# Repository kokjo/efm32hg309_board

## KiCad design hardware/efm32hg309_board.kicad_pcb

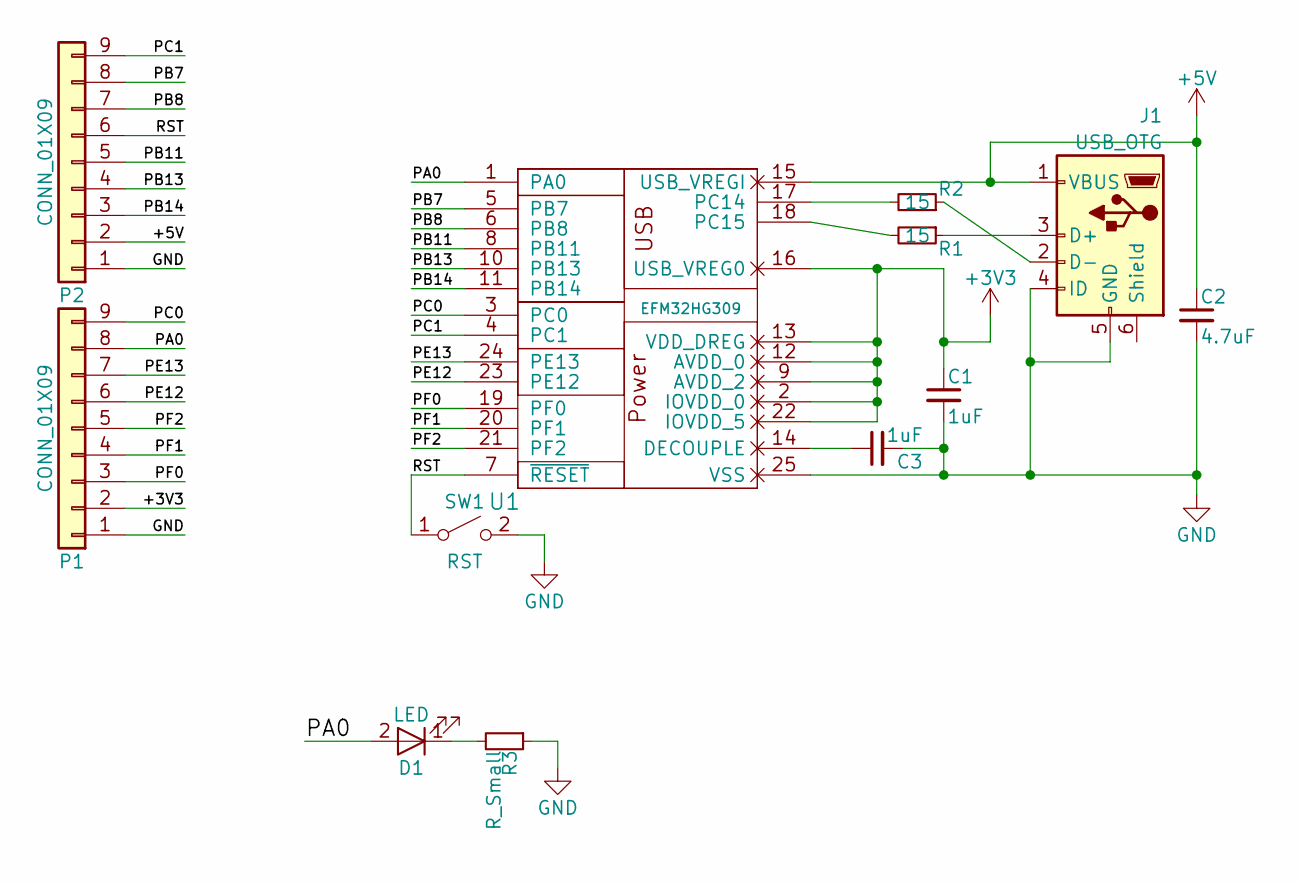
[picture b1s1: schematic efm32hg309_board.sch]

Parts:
C1, C3: 1uF; C_0805
C2: 4.7uF; C_0805
D1: LED; LED_0805
J1: USB_OTG; USB_Micro-B_Molex_47346-0001
P1, P2: CONN_01X09; Pin_Header_Straight_1x09
R1, R2: 15; R_0805
R3: R_Small; R_0805
SW1: RST; SW_SPST_B3U-1000P
U1: EFM32HG309; QFN-24-1EP_5x5mm_Pitch0.65mm

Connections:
+3V3: C1.1, P1.2, U1.2 (IOVDD_0), U1.9 (AVDD_2), U1.12 (AVDD_0), U1.13 (VDD_DREG), U1.16 (USB_VREG0), U1.22 (IOVDD_5)
+5V: C2.1, J1.1 (VBUS), P2.2, U1.15 (USB_VREGI)
/PA0: D1.2 (A), P1.8, U1.1 (PA0)
/PB7: P2.8, U1.5 (PB7)
/PB8: P2.7, U1.6 (PB8)
/PB11: P2.5, U1.8 (PB11)
/PB13: P2.4, U1.10 (PB13)
/PB14: P2.3, U1.11 (PB14)
/PC0: P1.9, U1.3 (PC0)
/PC1: P2.9, U1.4 (PC1)
/PE12: P1.6, U1.23 (PE12)
/PE13: P1.7, U1.24 (PE13)
/PF0: P1.3, U1.19 (PF0)
/PF1: P1.4, U1.20 (PF1)
/PF2: P1.5, U1.21 (PF2)
/RST: P2.6, SW1.1 (A), U1.7 (~RESET)
GND: C1.2, C2.2, C3.2, J1.4 (ID), J1.5 (GND), P1.1, P2.1, R3.1, SW1.2 (B), U1.25 (VSS)
unnamed: C3.1, U1.14 (DECOUPLE)
unnamed: D1.1 (K), R3.2
unnamed: J1.2 (D-), R2.1
unnamed: J1.3 (D+), R1.1
unnamed: R1.2, U1.18 (PC15)
unnamed: R2.2, U1.17 (PC14)

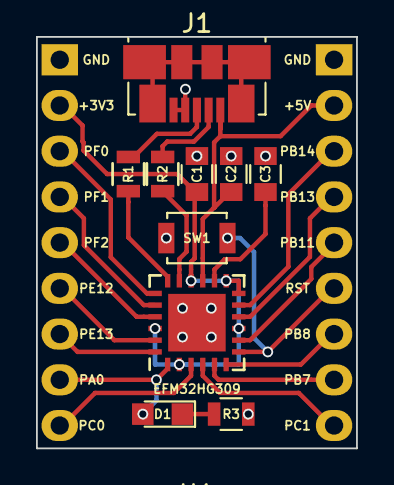
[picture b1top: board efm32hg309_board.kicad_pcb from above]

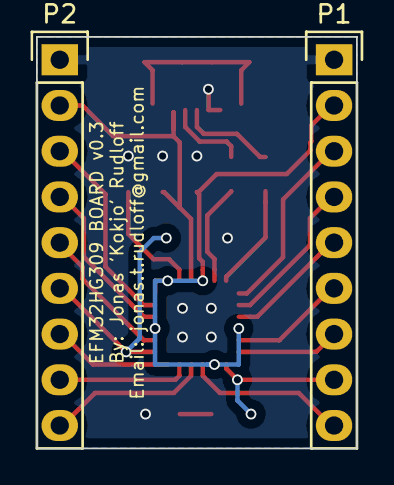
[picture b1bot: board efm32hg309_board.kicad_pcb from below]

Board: 2 copper layers, 17.8 x 22.9 mm, 12 parts (2 on the bottom side), 23 nets.

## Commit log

2018-04-23 initial commit of hardware
2018-04-23 cleaned up board
